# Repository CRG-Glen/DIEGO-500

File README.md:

# DIEGO PROJECT

Turn your A500 or Checkmate A1500 into an A2000 with this sidecar backplane.

## What's this?  

DIEGO is a Zorro 2 backplane expansion for use on your A500 either as a side car project or within your Checkmate case.  Diego gives you an A2000 compatible CO-PROCESSOR slot (side car version only) along with a full set of 5 ZORRO2 slots all made possible by the onboard Bluster IC.  Bluster is a remake of the classic A2000 Buster chip by LIV2 although it is a custom version for DIEGO to handle inverted clocks and provide some further functions.  

DIEGO has been tested extensively with various CPU and Zorro cards, a list of tested cards is provided below.  If you have anything to add to this list, please get in touch.  

DIEGO is also intended to power your A500 via the passthrough 4 pin connector adjacent to the main 24 pin ATX connector.  Please note that on the Checkmate version has power connected at the side car but also space for a passthrough.  The side car version currently does not have power connected at the side car.  For this version you must use the pass through to power your A500.  

## Ordering

There are currently 3 versions of DIEGO, a side car 5 slot version, a side car 3 slot version and a version for installation within a Checkmate case.  

Gerber, BOM and CPL files are provided for each in the JLCPCB folder.  

All passives on each version are located on the bottom side (with exception of ferrite bead on checkmate version and 5-SLOT-REV-1-2).  All logic and electrolytic caps are located on the top side.  

Each version of DIEGO is a 4 layer board.  HASL finish is fine for this project, inner layers can be left 0.5oz.  

All signals are routed on the top and bottom layers but there are some power traces on each internal layer along with solid grounds. Checkmate version has some internal signal traces, this was unavoidable in the limited space available.  

Due to the amount of passives I recommend having your PCB manufacturer fit the bottom side, you then as builder complete the top side.  

NOTES: 
1. At present the 3 slot version has not been tested so build at your own risk.
2. The 5 slot side car now has 2 versions.  Rev1-1 is the last production version that has been well tested and verified working with boards as per the list below.  Rev-1-2 has been redesigned with a solid internal ground and 5V flood fills however as yet has not been tested.  It should work fine but if anyone builds it please let me know.
3. The Checkmate version has been tested with my collection of Zorro 2 cards and works fine but is yet to be tested with DMA capable cards, I've no reason to think it won't work, it's just not as yet tested.  

## Assembly

Assuming you got your boards made with the bottom side completed you may fit out the top side to suit yourself.  I recommend fitting and programming the CPLD first and finish all SMD work before doing the slots as they'll just get in the way!  

NOTE (side car version only): U11 is only required if you're using something in the COPROCESSOR slot that needs a 28mhz clock.  There doesn't seem to be that many (if any) cards that do require this so you may leave this off if you prefer. (this has not been tested as I don't have anything that needs this clock)

FURTHER NOTE: You MUST use LS and ALS logic as per the BOM.  DIEGO was originally built with HCT logic but this caused issues with several boards.  HCT will work if you prefer to use this but you might find some early SCSI cards don't work.  

For the 86pin slot to the A500 on the side car version you will need to bend the pins in to meet the pads on DIEGO.  

For programming the CPLD, the required JED file is available in the CPLD folder or you may get it from LIV2s GitHub.  I use a Raspberry PI to programme CPLDs as per LIV2s guide but use whatever method you're comfortable with.  Just remember if using a PI and if powering 3.3v from the PI, disconnect all other power supplies from DIEGO!

## Using your DIEGO

For the most part DIEGO is simply plug and play but there are a few things to keep in mind.
- Firstly there is a single jumper to configure to select which 7mhz clock to use.  If you're using a Rev3 or 5 A500 you must select CPLD clock.  If you're using a Rev6 A500 you can use either but if using A500 clock you need to close JP6 on the A500s motherboard.  If you are using an A500+ you can pick either.  The CPLD clock is derived from _CCK XNOR _CCQK within the CPLD.    
- There is one more pin header labelled CFGIN.  If you have any expansions in your A500 on the autoconfig chain you MUST connect said expansions config out to this config in.  If you don't you'll most likely get a yellow screen or just no zorro cards detected!
- Insert all cards as if this was a real A2000 i.e. the front of DIEGO is the front of an A2000.  Most modern Zorro expansions (especially half length cards) will have an arrow pointing to front or back.  Pay attention to this! If you plug something in wrong expect a dead card and possibly dead Amiga! 
- Zorro 2 cards will autoconfigure themselves just like they would in any Amiga.  To confirm this hold both mouse buttons on start up to access the early start-up menu and select "expansion board diagnostic" (only available to kickstart 2.04 and up)

Side car version only
-  If you're using a true A2000 CPU card in the COPROCESSOR slot (like the N2630) simply insert the card and Bluster will tristate the internal A500 CPU. (this is achieved by Bluster monitoring _BOSS and when asserted, Bluster asserts _BR to the internal CPU)  
- If you're using an A500 type accelerator in the COPROCESSOR slot such as TF536 or a PISTORM (including PISTORM 2000), you MUST open the A500 and remove the internal CPU.  Even if you manually assert _BOSS, the E clocks will clash and it won't work.  There is NO fix for this!  A2000 accelerators work as they monitor E and sync to it or generate it as necessary.  

Checkmate version only
- If you're using an accelerator in the A500s CPU socket you may need to connect its config out to the config in pin on DIEGO.  If you get a yellow screen or crash on boot this is the likely cause.  

## Testing and Results

With thanks to GADGETUK, SPARX, CATHERS, ANDI@HBR and Xanxi-Amiga we've been able to test and confirm that most boards 
work fine in DIEGO.  The below table lists those boards tested and confirmed as working or not.  These have all been tested and verified on Sidecar 5SLOT-REV1-1

| Card Type | Name | Status |
|---|---|---|
| SCSI | Commodore A2090A | Working but very fussy (requires LS and ALS logic).  Only bluescsi V2 and only in raw mode. |
| SCSI | Commodore A2091 | Working |
| SCSI | GVP Series II HC+8 | Working |
| IDE |	Ripple IDE | Working |
| IDE |	AT-Bus clone | Working |
| IDE |	Buddha | Working |
| RAM |	Amigakit ZORRAM | Working |
| RAM |	Gottagofastram 2000 | Working |
| Sound | Prelude | Working |
| Sound | Toccata | Working |
| Sound | AD516 audio card | Working |
| RTG |	GBAPII | Working |
| RTG |	Merlin | Working |
| Networking |	Hydranet | Working |
| IO | BSC Multiface 3 | Working |
| IO | Thylacine USB (old longer model) | Working |
| Multi-feature | LAN-IDE-Clock | Working/Working/Not tested |
| CPU |	A2630 | Working |
| CPU |	N2630 | Working |
| CPU |	TF520 | Working |
| CPU |	TF536 | Working |
| CPU |	TK2 | Working |
| CPU |	Pistorm | Working |
| CPU |	Pistorm 2k | Working |
| Bridgeboard |	Commodore A2286 | Working |
| Bridgeboard |	Commodore A2086 | Working |

If you can add to this table please get in touch!

## Case

At present there is no full case but there is a base that will hold either the 3 or 5 slot version of Diego level with the side car slot of your A500.  I'm not great at designing these things so if you want to help please get in touch.  STL files are in the BASE folder.  

With thanks to Maikiro on Discord we now had a proper base for the 5 slot version.  He has kindly created 3 version of this to suit positioning of your ATX power connector.  STLs for these are provided in the BASE/Maikiro folder.

## FAQ

Several people have asked about adding ISA slots, a video slot or making this remote with a ribbon cable to the A500.  

ISA slots - DIEGO side car has been designed so that you could in theory add ISA slots on a separate board, the Zorro slots 
in relation to the edge of the PCB are positioned to allow this.  I haven't designed an ISA slot extension as I don't have a bridge board to test it with.  
The Checkmate version could be redesigned to incorporate ISA slots although you will loose 2 of the half length zorro slots.  For this release it was thought more useful to include 5 zorro slots. 

Video slot - There are no plans to add a video slot.  Very few of the required signals are on the A500s side car so it would need a multicore ribbon from DENISE.  

Ribbon Cable for remote use - If you want to try a ribbon cable to have DIEGO remote from your 500 you can simply solder one onto the edge connector but I don't expect this to work without further buffering! (like in the bodega bay).

A1000 version - This is coming along with a rework of the entire project to sit vertical beside your 500.  It'll take a while to figure out so please bear with me.  

## License

This project represents countless hours of work by not just me but LIV2 and everyone involved in testing.  It is however released under a CERN Open Hardware Licence v2 for the community to enjoy.  

While I cannot put any direct stipulations into this I would ask that it should only be built and sold at cost plus time.  

If you plan on forking or using this as the basis for any other works you must comply with the following as per the terms of the license attributed to this project.
1. All attributions and credits as presented within this github and on the DIEGO PCBs must be maintained and carried through.
2. Any derivative of this project must be also be released open source.

If you are doing a build of these please consider a £1 donation per board to my kofi - https://ko-fi.com/crg_glen.  I'm at least £500 into this project so any support to recoup this is appreicated.  

## Credits

Based on A2000 rev6 schematics by Dave Haynie and EATX2000 by Jasonsbeer

PCB by CRG(Glen)

Bluster by LIV2

Artwork by Brick Studios

Testing by GadgetUK, Sparx, Cathers and Andi@HBR

REV1-2 Redesign by Jimbro1000

Thanks to Mikerochip for inspiration for the PSU switch, Neil from Retro4U for loaning his GVP for testing and Kazanoz for helping with the BOM

Special thanks to GadgetUK for hosting the test room on his discord and LIV2 for his work modifying Bluster

Extra Special thanks to Rob Cranley and Steve Jones for their help on the Checkmate version

Why is it called Diego?  Well... this project started solely as a Zorro 2 expansion and to implement that I first had
to understand how the Zorro bus worked.  You might say I had to unmask Zorro.  The character of Zorro unmasked is called Don Diego so Diego 500 or Diego Checkmate.

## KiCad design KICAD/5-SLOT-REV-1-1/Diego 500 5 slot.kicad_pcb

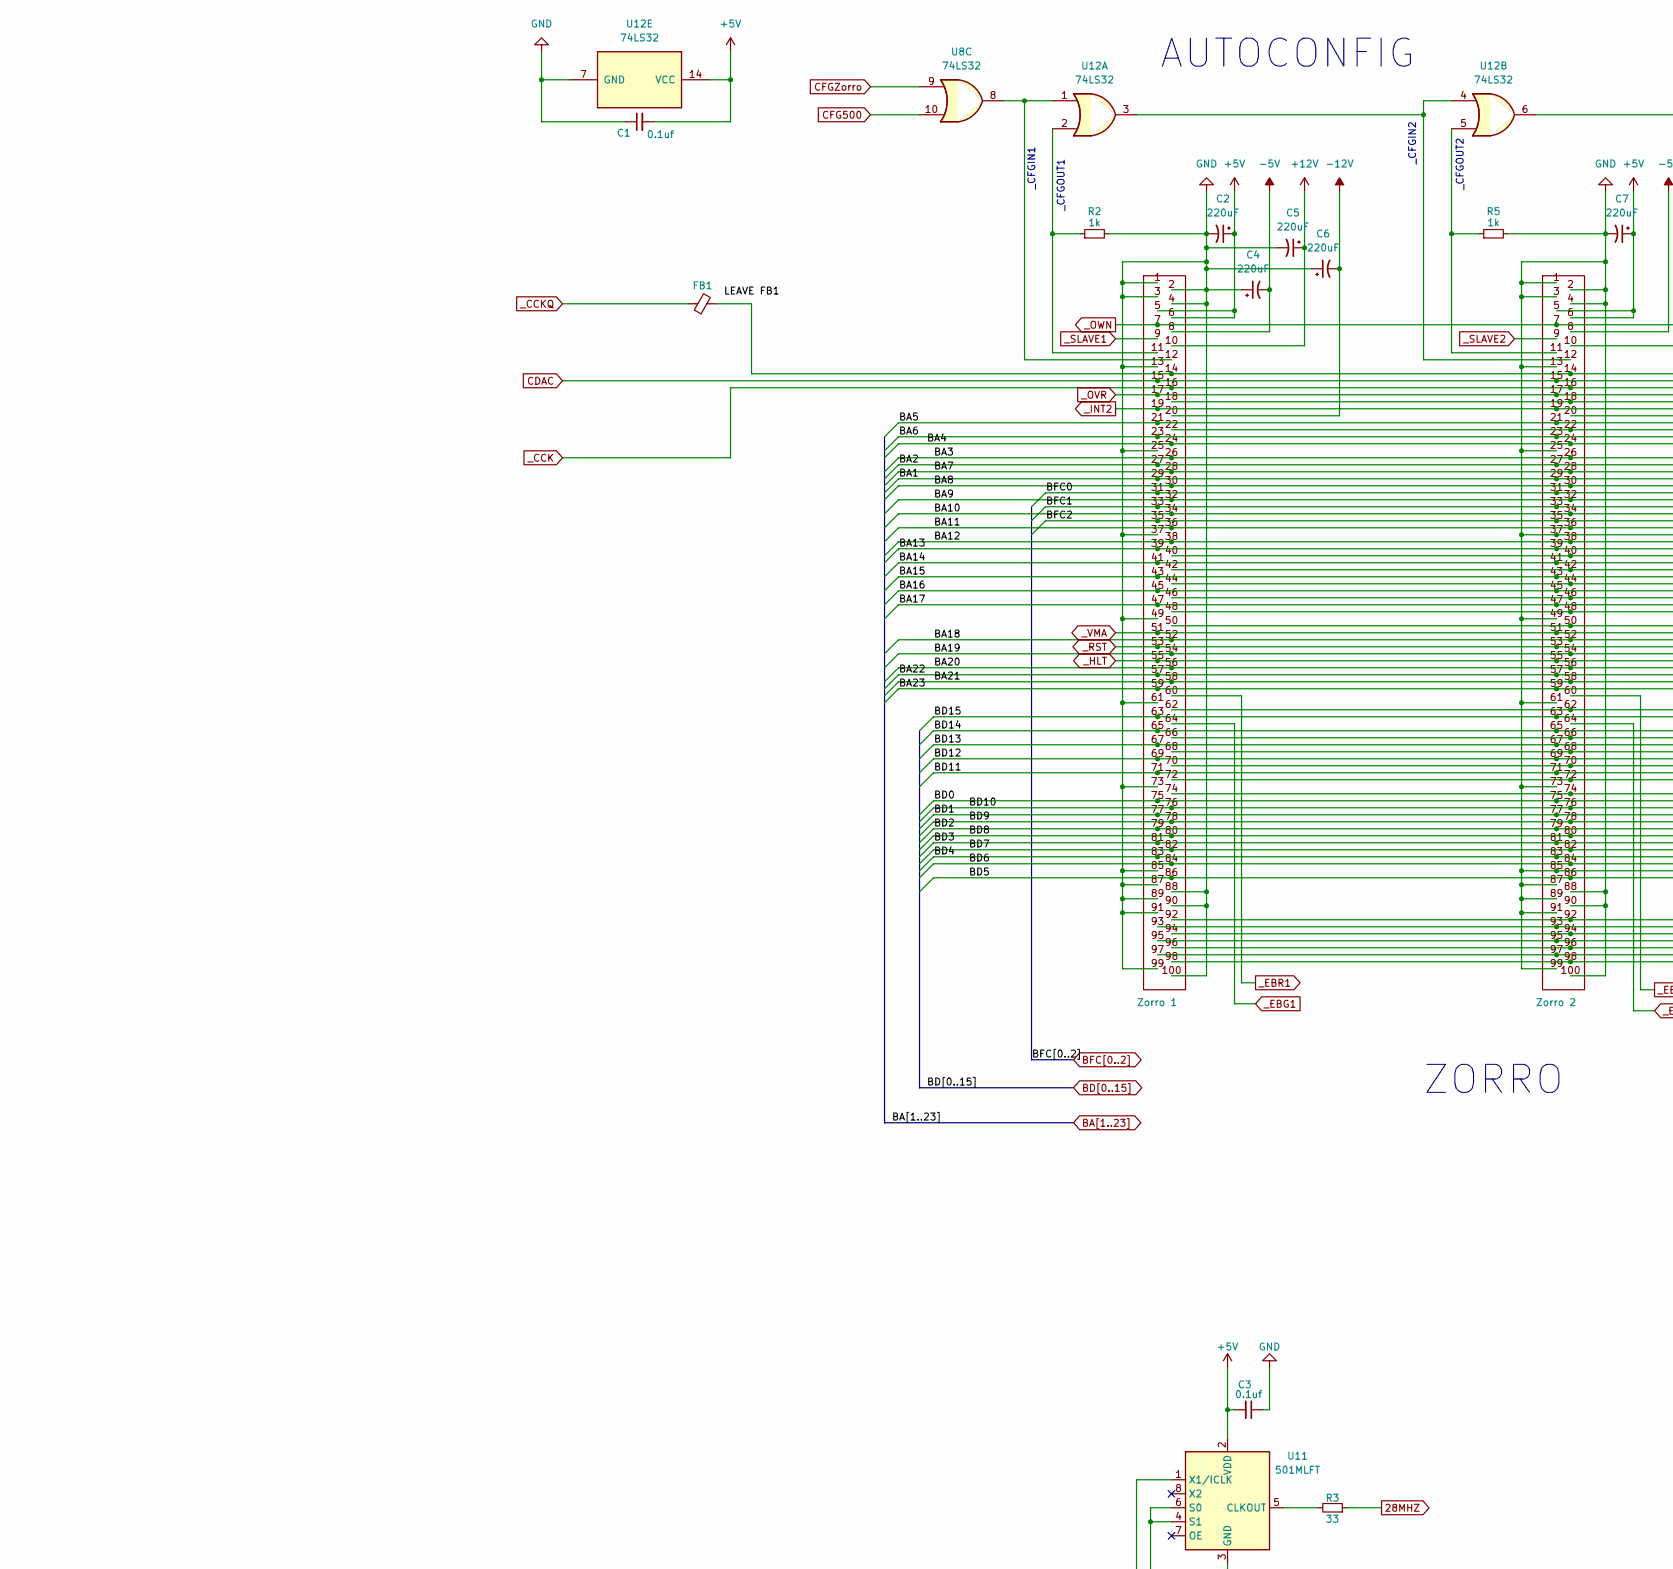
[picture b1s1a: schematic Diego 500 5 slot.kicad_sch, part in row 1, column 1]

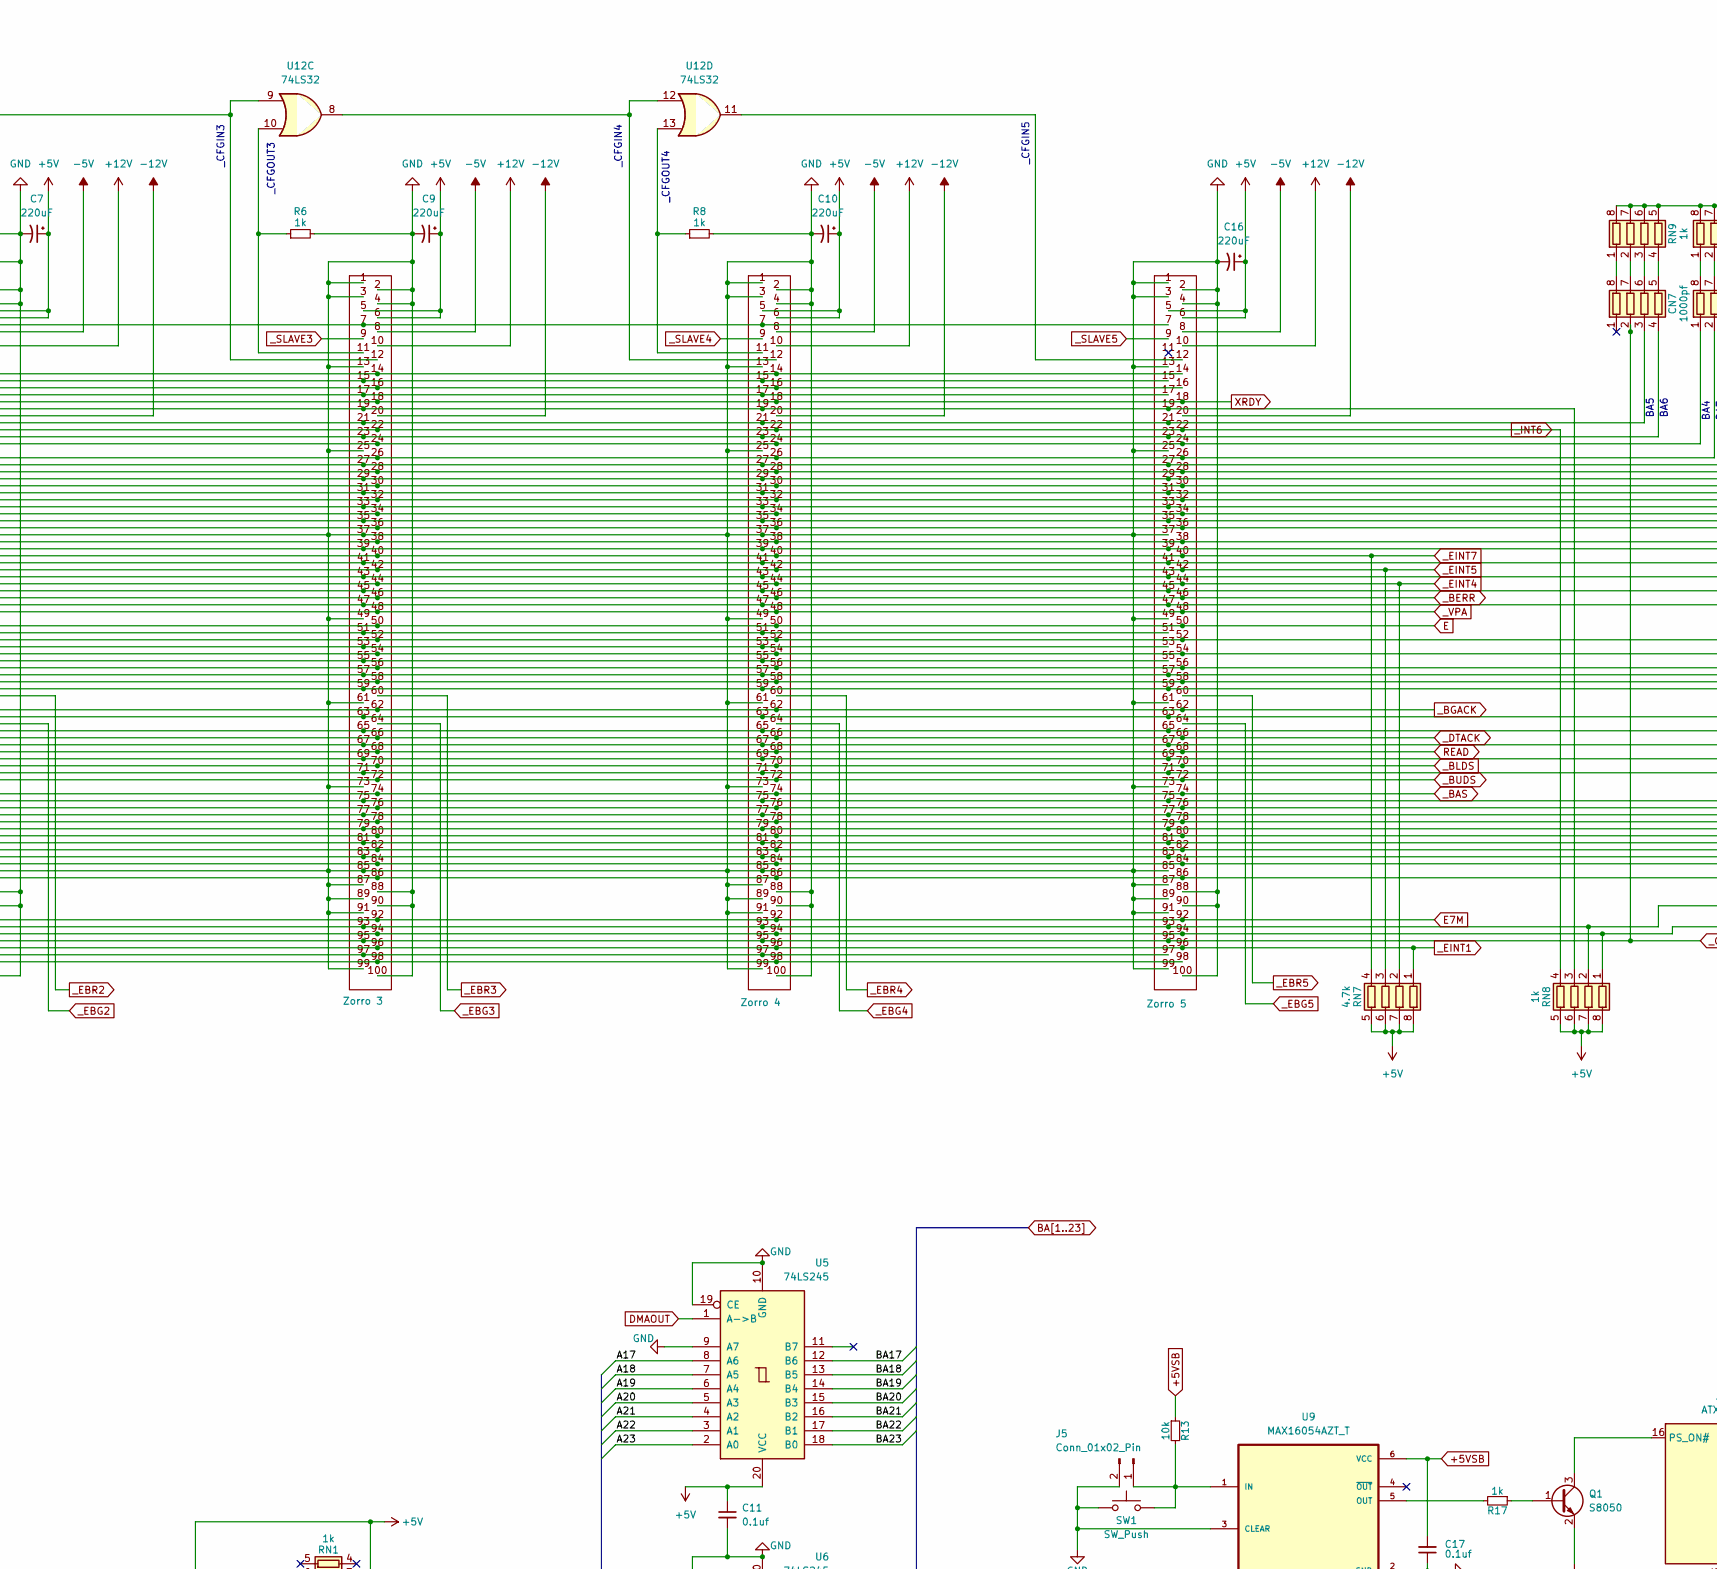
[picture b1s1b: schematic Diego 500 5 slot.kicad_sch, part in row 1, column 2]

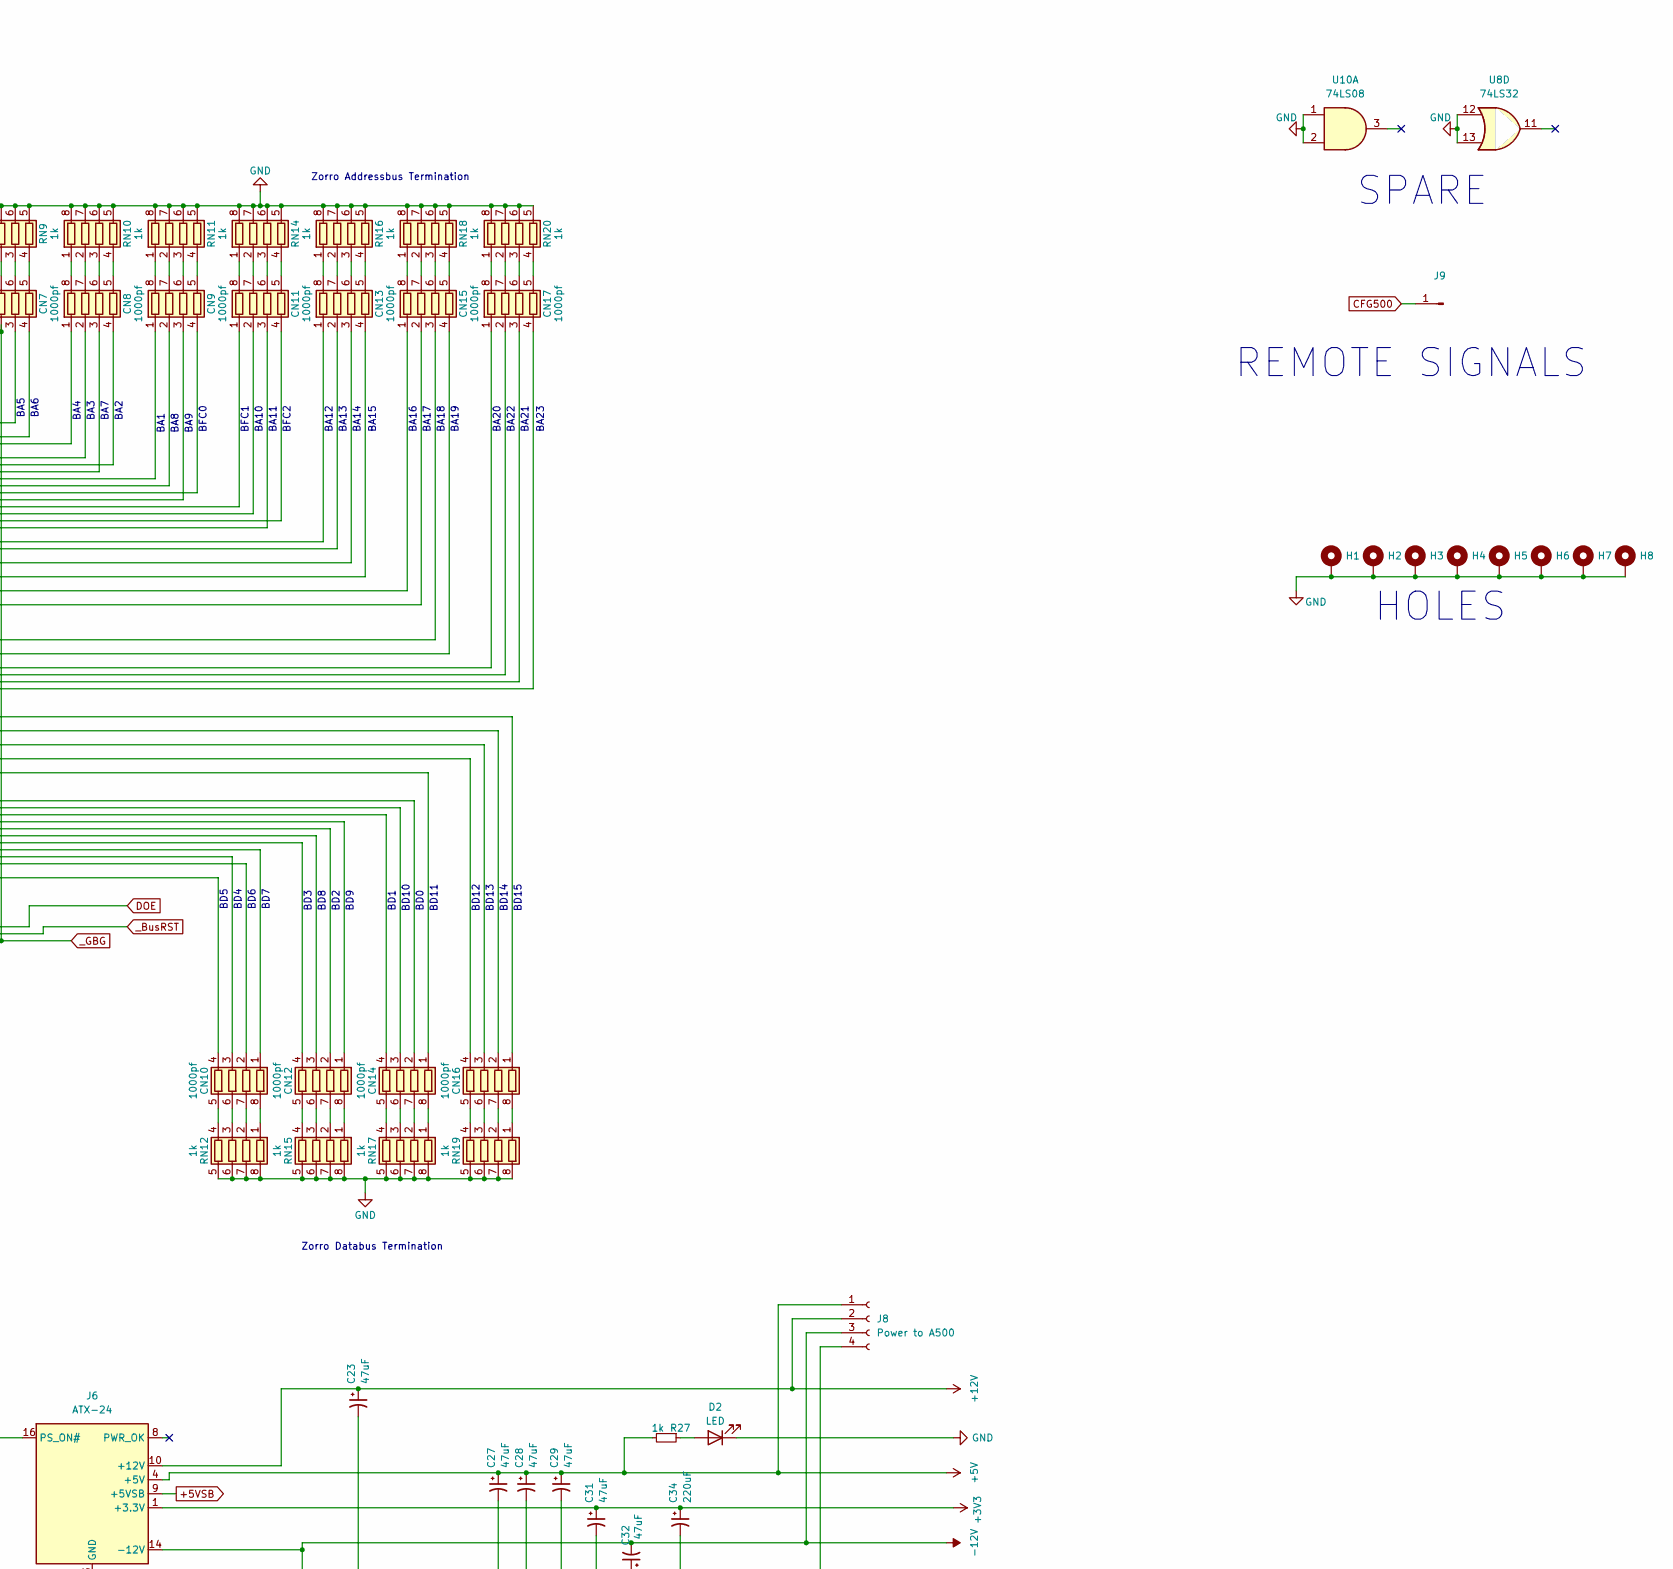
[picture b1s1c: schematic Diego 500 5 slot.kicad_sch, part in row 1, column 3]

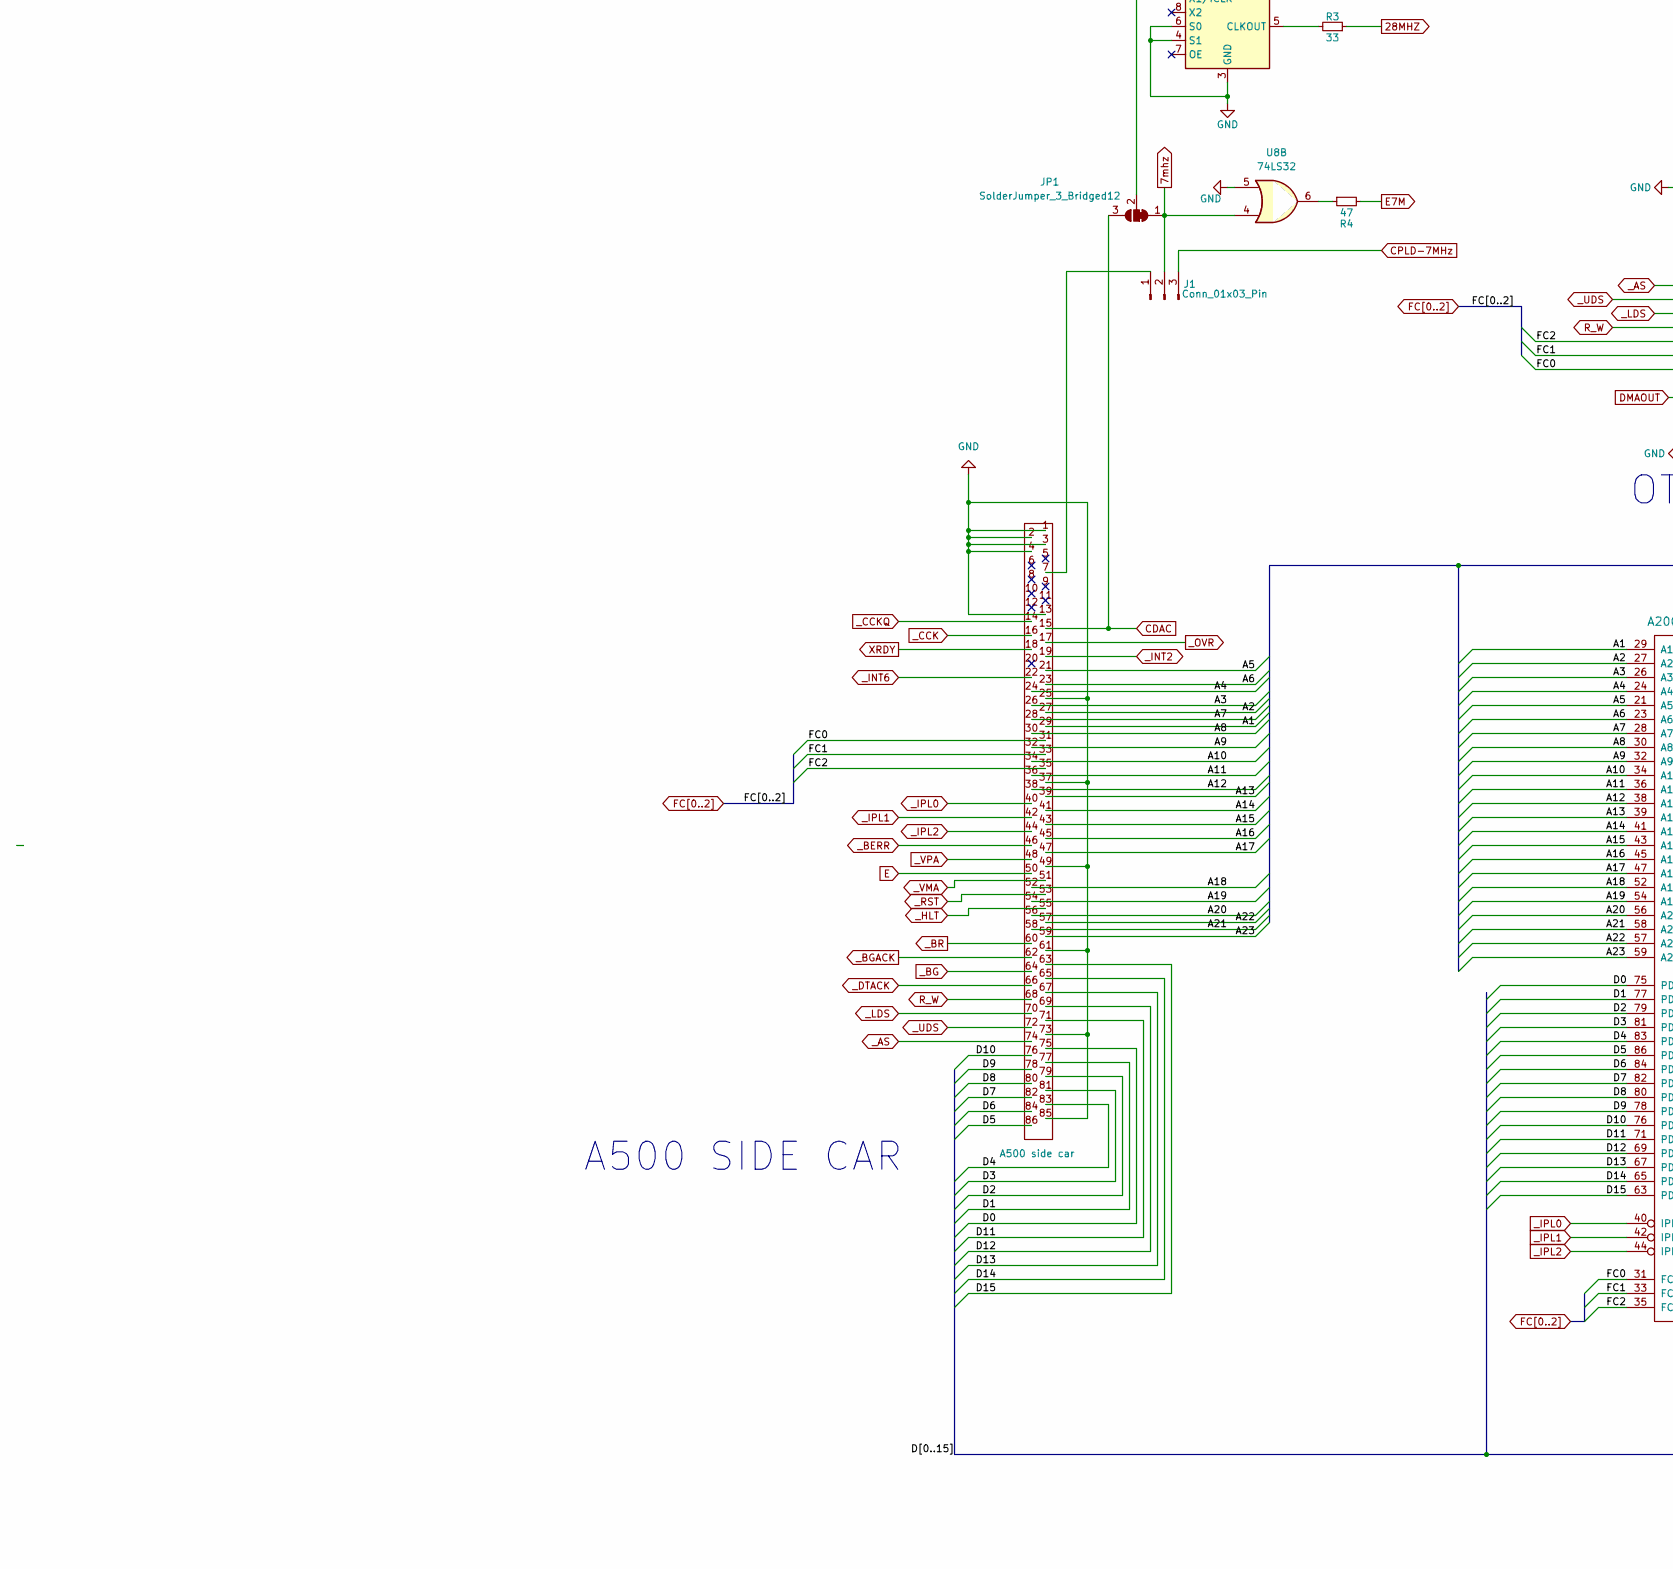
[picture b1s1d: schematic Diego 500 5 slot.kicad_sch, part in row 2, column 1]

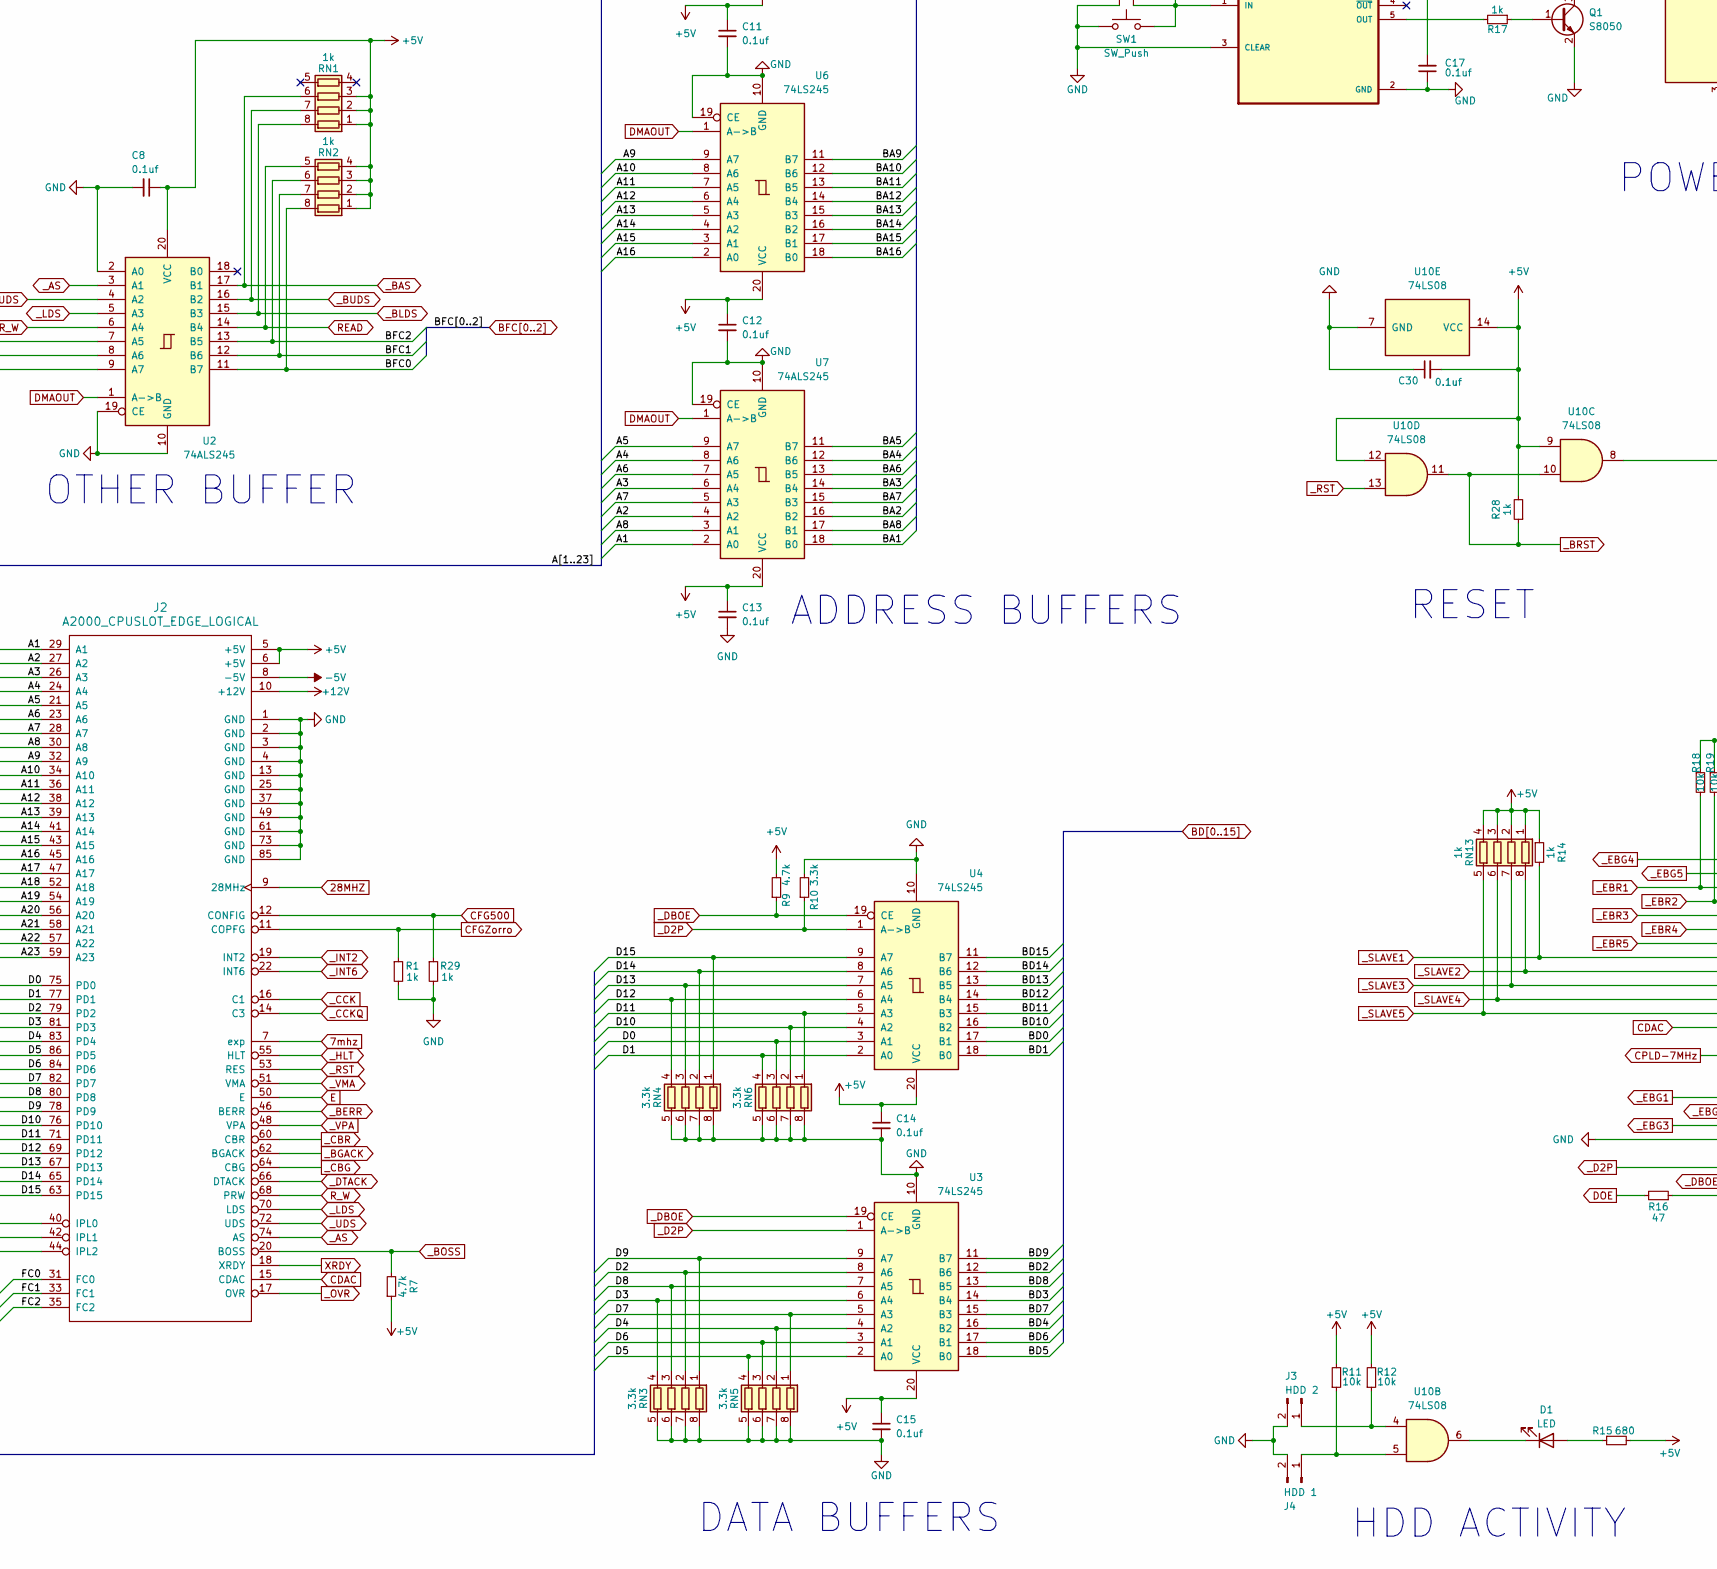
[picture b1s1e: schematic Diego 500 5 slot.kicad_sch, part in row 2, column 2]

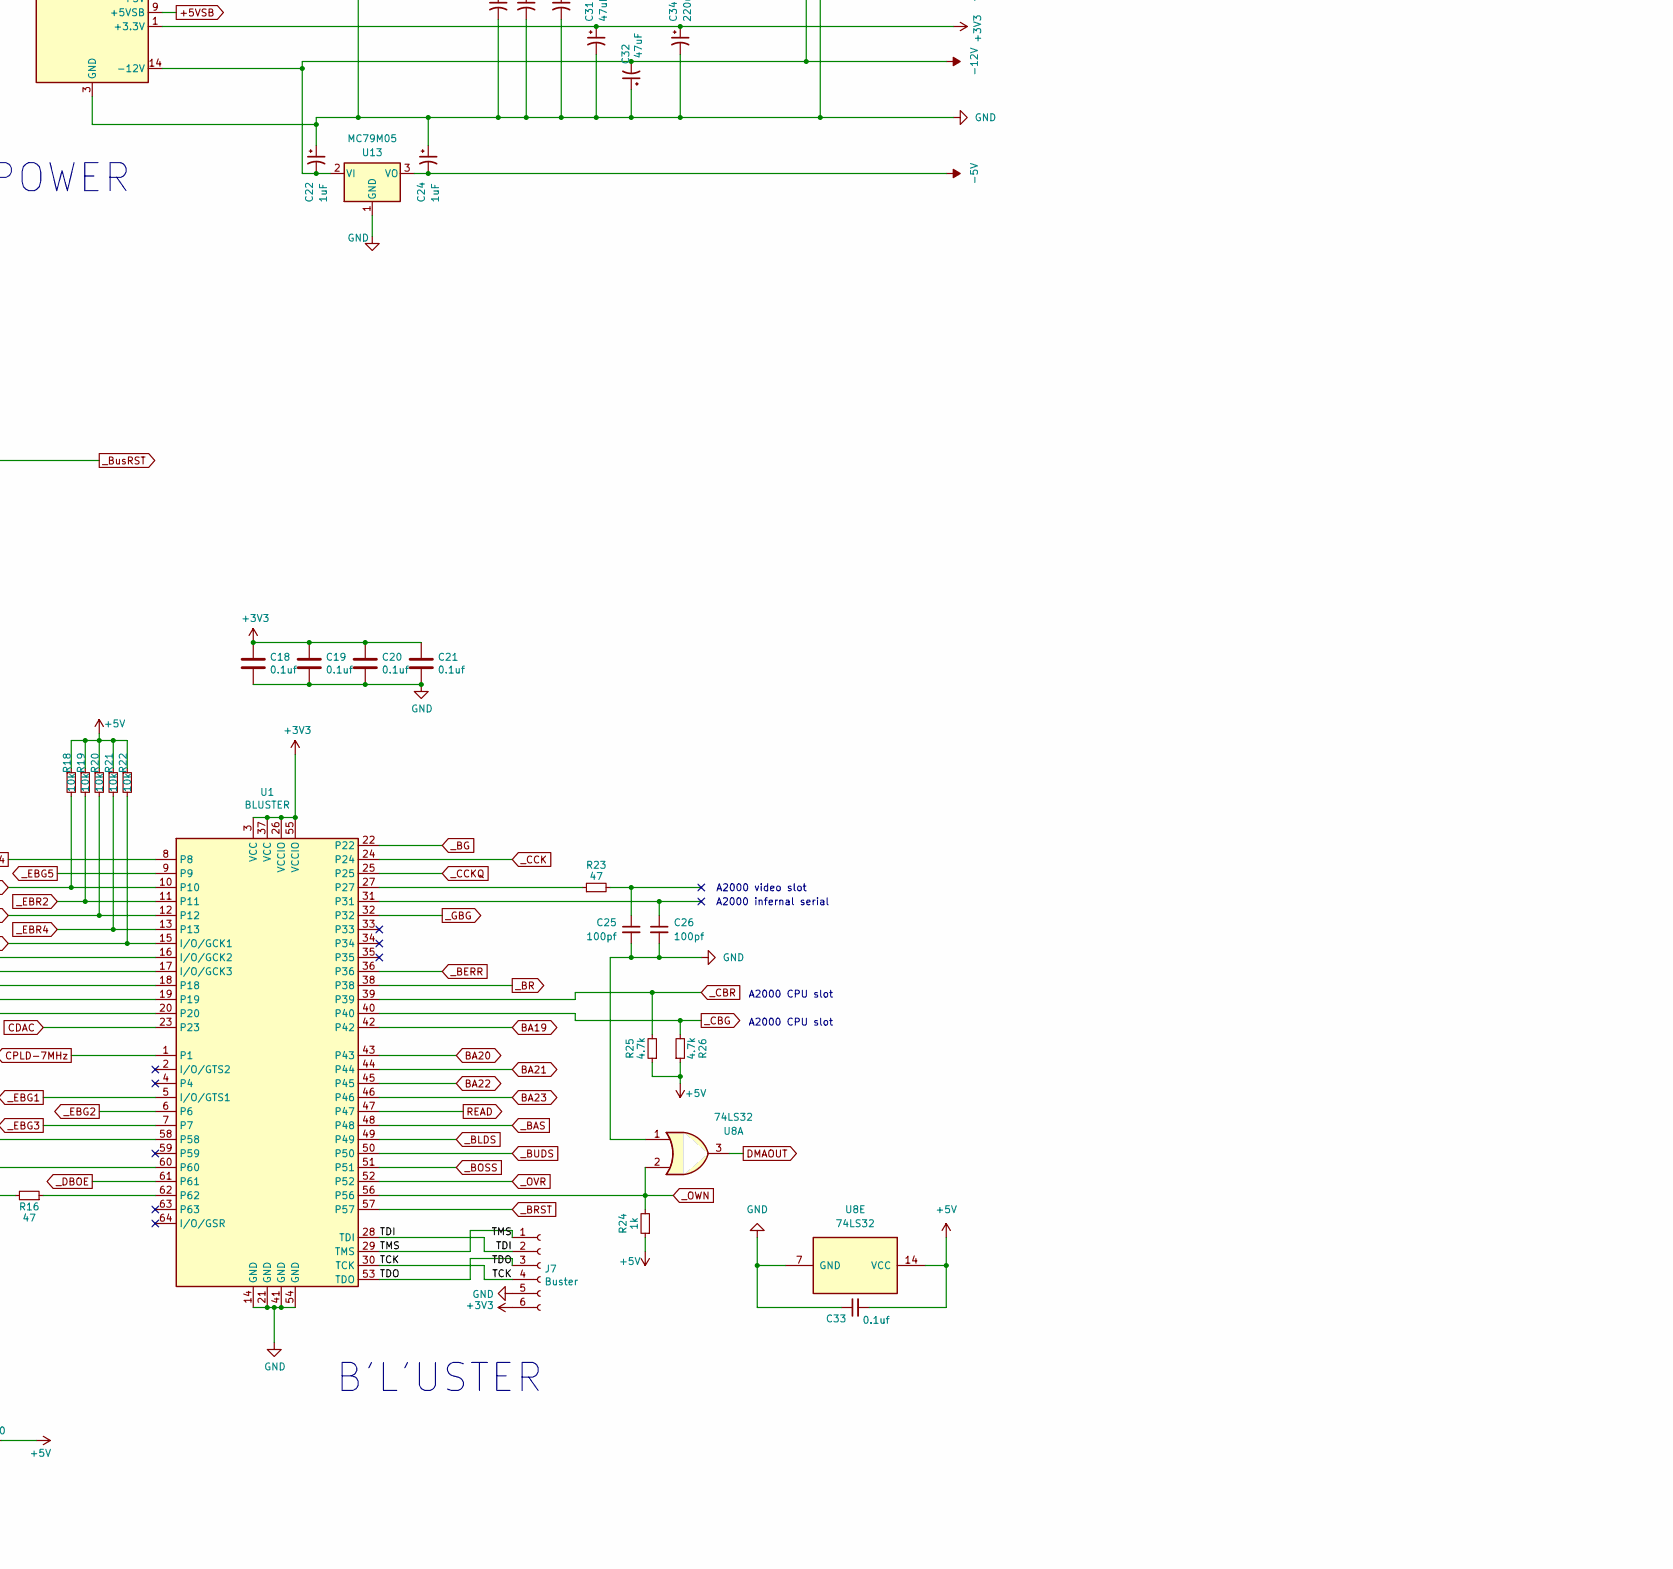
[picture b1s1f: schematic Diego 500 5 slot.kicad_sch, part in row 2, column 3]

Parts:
C1, C3, C8, C11, C12, C13, C14, C15, C17, C30, C33: 0.1uf; C_0805_2012Metric; LCSC C49678
C2, C4, C5, C6, C7, C9, C10, C16, C34: 220uF; CP_Elec_6.3x7.7; LCSC C278407
C18, C19, C20, C21: 0.1uf; C_0805_2012Metric_Pad1.18x1.45mm_HandSolder; LCSC C49678
C22, C24: 1uF; CP_Elec_4x5.4; LCSC C3348
C23, C27, C28, C29, C31, C32: 47uF; CP_Elec_6.3x7.7; LCSC C336249
C25, C26: 100pf; C_0805_2012Metric; LCSC C1790
CN1: A500 side car; A500_SIDE_CONNECTOR
CN2: Zorro 1; Samtec_HLE-150-02-xx-DV-TE_2x50_P2.54mm_Horizontal
CN3: Zorro 2; Samtec_HLE-150-02-xx-DV-TE_2x50_P2.54mm_Horizontal
CN4: Zorro 3; Samtec_HLE-150-02-xx-DV-TE_2x50_P2.54mm_Horizontal
CN5: Zorro 4; Samtec_HLE-150-02-xx-DV-TE_2x50_P2.54mm_Horizontal
CN6: Zorro 5; Samtec_HLE-150-02-xx-DV-TE_2x50_P2.54mm_Horizontal
CN7, CN8, CN9, CN10, CN11, CN12, CN13, CN14, CN15, CN16, CN17: 1000pf; R_Array_Convex_4x0603; LCSC C541606
D1: LED; LED_1206_3216Metric_Pad1.42x1.75mm_HandSolder; LCSC C49018
D2: LED; LED_1206_3216Metric_Pad1.42x1.75mm_HandSolder; LCSC C14641
FB1: FerriteBead_Small; D_0805_2012Metric; LCSC C1015
H1, H2, H3, H4, H5, H6, H7, H8: MountingHole_Pad; MountingHole_3.2mm_M3_DIN965_Pad
J1: Conn_01x03_Pin; PinHeader_1x03_P2.54mm_Vertical
J2: A2000_CPUSLOT_EDGE_LOGICAL; Samtec_HLE-150-02-xx-DV-TE_2x43_P2.54mm_Horizontal
J3: HDD 2; PinHeader_1x02_P2.54mm_Vertical
J4: HDD 1; PinHeader_1x02_P2.54mm_Vertical
J5: Conn_01x02_Pin; PinHeader_1x02_P2.54mm_Vertical
J6: ATX-24; Molex_Mini-Fit_Jr_5569-24A2_2x12_P4.20mm_Horizontal
J7: Buster; PinHeader_1x06_P2.54mm_Vertical
J8: Power to A500; Molex_Mini-Fit_Jr_5569-04A2_2x02_P4.20mm_Horizontal
J9: Conn_01x01_Pin; PinHeader_1x01_P2.54mm_Vertical
JP1: SolderJumper_3_Bridged12; SolderJumper-3_P1.3mm_Bridged12_RoundedPad1.0x1.5mm
Q1: S8050; SOT-23; LCSC C2146
R1, R2, R5, R6, R8, R14, R17, R24, R28, R29: 1k; R_0805_2012Metric; LCSC C17513
R3: 33; R_0805_2012Metric; LCSC C17634
R4, R16, R23: 47; R_0805_2012Metric; LCSC C17714
R7, R9, R25, R26: 4.7k; R_0805_2012Metric; LCSC C17673
R10: 3.3k; R_0805_2012Metric; LCSC C26010
R11, R12, R13, R18, R19, R20, R21, R22: 10k; R_0805_2012Metric; LCSC C17414
R15: 680; R_0805_2012Metric; LCSC C17798
R27: 1k; R_0805_2012Metric; LCSC C17798
RN1, RN2, RN8, RN9, RN10, RN11, RN12, RN13, RN14, RN15, RN16, RN17, RN18, RN19, RN20: 1k; R_Array_Convex_4x0603; LCSC C20197
RN3, RN4, RN5, RN6: 3.3k; R_Array_Convex_4x0603; LCSC C102665
RN7: 4.7k; R_Array_Convex_4x0603; LCSC C66697
SW1: SW_Push; SW_PUSH_1P1T_6x3.5mm_H4.3_APEM_MJTP1243
U1: BLUSTER; TQFP-64_10x10mm_P0.5mm; LCSC C90569
U2, U7: 74ALS245; SO-20_5.3x12.6mm_P1.27mm; LCSC C2675885
U3, U4, U5, U6: 74LS245; SO-20_5.3x12.6mm_P1.27mm; LCSC C7753
U8, U12: 74LS32; SO-14_3.9x8.65mm_P1.27mm; LCSC C116812
U9: MAX16054AZT_T; SOT95P275X110-6N; LCSC C79401
U10: 74LS08; SO-14_3.9x8.65mm_P1.27mm; LCSC C6802
U11: 501MLFT; SOIC-8_3.9x4.9mm_P1.27mm; LCSC C2651221
U13: MC79M05; TO-252-2; LCSC C126401

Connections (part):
7mhz: J1.2, J2.7 (exp), JP1.1 (A), U8.4
28MHZ: J2.9 (28MHz), R3.1
+3V3: C18.1, C19.1, C20.1, C21.1, C31.1, C34.1, J6.1 (+3.3V), J6.2 (+3.3V), J6.12 (+3.3V), J6.13 (+3.3V), J7.6, U1.3 (VCC), U1.26 (VCCIO), U1.37 (VCC), U1.55 (VCCIO)
+5V: C1.2, C2.1, C3.2, C7.1, C8.1, C9.1, C10.1, C11.1, C12.1, C13.1, C14.1, C15.1, C16.1, C27.1, C28.1, C29.1, C30.2, C33.2, CN2.5, CN2.6, CN3.5, CN3.6, CN4.5, CN4.6, CN5.5, CN5.6, CN6.5, CN6.6, J2.5 (+5V), J2.6 (+5V), J6.4 (+5V), J6.6 (+5V), J6.21 (+5V), J6.22 (+5V), J6.23 (+5V), J8.1, R7.1, R9.2, R11.2, R12.2, R14.1, R15.2, R18.1, R19.1, R20.1, R21.1, R22.1, R24.1, R25.1, R26.1, R27.2, R28.2, RN1.1 (R1.1), RN1.2 (R2.1), RN1.3 (R3.1), RN2.1 (R1.1), RN2.2 (R2.1), RN2.3 (R3.1), RN2.4 (R4.1), RN7.5 (R4.2), RN7.6 (R3.2), RN7.7 (R2.2), RN7.8 (R1.2), RN8.5 (R4.2), RN8.6 (R3.2), RN8.7 (R2.2), RN8.8 (R1.2), RN13.1 (R1.1), RN13.2 (R2.1), RN13.3 (R3.1), RN13.4 (R4.1), U2.20 (VCC), U3.20 (VCC), U4.20 (VCC), U5.20 (VCC), U6.20 (VCC), U7.20 (VCC), U8.14 (VCC), U10.9, U10.12, U10.14 (VCC), U11.2 (VDD), U12.14 (VCC); also elsewhere on the board
+5VSB: C17.2, J6.9 (+5VSB), R13.1, U9.6 (VCC)
+12V: C5.1, C23.1, CN2.10, CN3.10, CN4.10, CN5.10, CN6.10, J2.10 (+12V), J6.10 (+12V), J6.11 (+12V), J8.2
-5V: C4.2, C24.2, CN2.8, CN3.8, CN4.8, CN5.8, CN6.8, J2.8 (-5V), U13.3 (VO)
-12V: C6.2, C22.2, C32.2, CN2.20, CN3.20, CN4.20, CN5.20, CN6.20, J6.14 (-12V), J8.3, U13.2 (VI)
/A1: CN1.29, J2.29 (A1), U7.2 (A0)
/A2: CN1.27, J2.27 (A2), U7.4 (A2)
/A3: CN1.26, J2.26 (A3), U7.6 (A4)
/A4: CN1.24, J2.24 (A4), U7.8 (A6)
/A5: CN1.21, J2.21 (A5), U7.9 (A7)
/A6: CN1.23, J2.23 (A6), U7.7 (A5)
/A7: CN1.28, J2.28 (A7), U7.5 (A3)
/A8: CN1.30, J2.30 (A8), U7.3 (A1)
/A9: CN1.32, J2.32 (A9), U6.9 (A7)
/A10: CN1.34, J2.34 (A10), U6.8 (A6)
/A11: CN1.36, J2.36 (A11), U6.7 (A5)
/A12: CN1.38, J2.38 (A12), U6.6 (A4)
/A13: CN1.39, J2.39 (A13), U6.5 (A3)
/A14: CN1.41, J2.41 (A14), U6.4 (A2)
/A15: CN1.43, J2.43 (A15), U6.3 (A1)
/A16: CN1.45, J2.45 (A16), U6.2 (A0)
/A17: CN1.47, J2.47 (A17), U5.8 (A6)
/A18: CN1.52, J2.52 (A18), U5.7 (A5)
/A19: CN1.54, J2.54 (A19), U5.6 (A4)
/A20: CN1.56, J2.56 (A20), U5.5 (A3)
/A21: CN1.58, J2.58 (A21), U5.4 (A2)
/A22: CN1.57, J2.57 (A22), U5.3 (A1)
/A23: CN1.59, J2.59 (A23), U5.2 (A0)
/D0: CN1.75, J2.75 (PD0), RN6.3 (R3.1), U4.3 (A1)
/D1: CN1.77, J2.77 (PD1), RN6.4 (R4.1), U4.2 (A0)
/D2: CN1.79, J2.79 (PD2), RN3.2 (R2.1), U3.8 (A6)
/D3: CN1.81, J2.81 (PD3), RN3.4 (R4.1), U3.6 (A4)
/D4: CN1.83, J2.83 (PD4), RN5.2 (R2.1), U3.4 (A2)
/D5: CN1.86, J2.86 (PD5), RN5.4 (R4.1), U3.2 (A0)
/D6: CN1.84, J2.84 (PD6), RN5.3 (R3.1), U3.3 (A1)
/D7: CN1.82, J2.82 (PD7), RN5.1 (R1.1), U3.5 (A3)
/D8: CN1.80, J2.80 (PD8), RN3.3 (R3.1), U3.7 (A5)
/D9: CN1.78, J2.78 (PD9), RN3.1 (R1.1), U3.9 (A7)
/D10: CN1.76, J2.76 (PD10), RN6.2 (R2.1), U4.4 (A2)
/D11: CN1.71, J2.71 (PD11), RN6.1 (R1.1), U4.5 (A3)
/D12: CN1.69, J2.69 (PD12), RN4.4 (R4.1), U4.6 (A4)
/D13: CN1.67, J2.67 (PD13), RN4.3 (R3.1), U4.7 (A5)
/D14: CN1.65, J2.65 (PD14), RN4.2 (R2.1), U4.8 (A6)
/D15: CN1.63, J2.63 (PD15), RN4.1 (R1.1), U4.9 (A7)
/TCK: J7.4, U1.30 (TCK)
/TDI: J7.2, U1.28 (TDI)
/TDO: J7.3, U1.53 (TDO)
/TMS: J7.1, U1.29 (TMS)
BA1: CN2.29, CN3.29, CN4.29, CN5.29, CN6.29, CN9.1 (R1.1), U7.18 (B0)
BA2: CN2.27, CN3.27, CN4.27, CN5.27, CN6.27, CN8.4 (R4.1), U7.16 (B2)
BA3: CN2.26, CN3.26, CN4.26, CN5.26, CN6.26, CN8.2 (R2.1), U7.14 (B4)
BA4: CN2.24, CN3.24, CN4.24, CN5.24, CN6.24, CN8.1 (R1.1), U7.12 (B6)
BA5: CN2.21, CN3.21, CN4.21, CN5.21, CN6.21, CN7.3 (R3.1), U7.11 (B7)
BA6: CN2.23, CN3.23, CN4.23, CN5.23, CN6.23, CN7.4 (R4.1), U7.13 (B5)
BA7: CN2.28, CN3.28, CN4.28, CN5.28, CN6.28, CN8.3 (R3.1), U7.15 (B3)
BA8: CN2.30, CN3.30, CN4.30, CN5.30, CN6.30, CN9.2 (R2.1), U7.17 (B1)
BA9: CN2.32, CN3.32, CN4.32, CN5.32, CN6.32, CN9.3 (R3.1), U6.11 (B7)
BA10: CN2.34, CN3.34, CN4.34, CN5.34, CN6.34, CN11.2 (R2.1), U6.12 (B6)
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
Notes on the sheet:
_CFGIN2
BA11
Zorro Addressbus Termination
AUTOCONFIG
BA18
BD14
BD15
BD1
BD4
BD11
BD9
BD6
BA1
BA3
BD2
BA21
BD13
BA16
BA15
BD0
BA20
POWER
OTHER BUFFER
SPARE
BA8
BD7
_CFGOUT3
BA2
HDD ACTIVITY
BFC0
REMOTE SIGNALS
BA23
BA5
BA22
BD8
BA4
A2000 video slot
RESET
_CFGIN5
BD5
